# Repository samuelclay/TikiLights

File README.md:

# TikiLights
Hand-held tiki lights with color customization and a 3d printed Tiki mask

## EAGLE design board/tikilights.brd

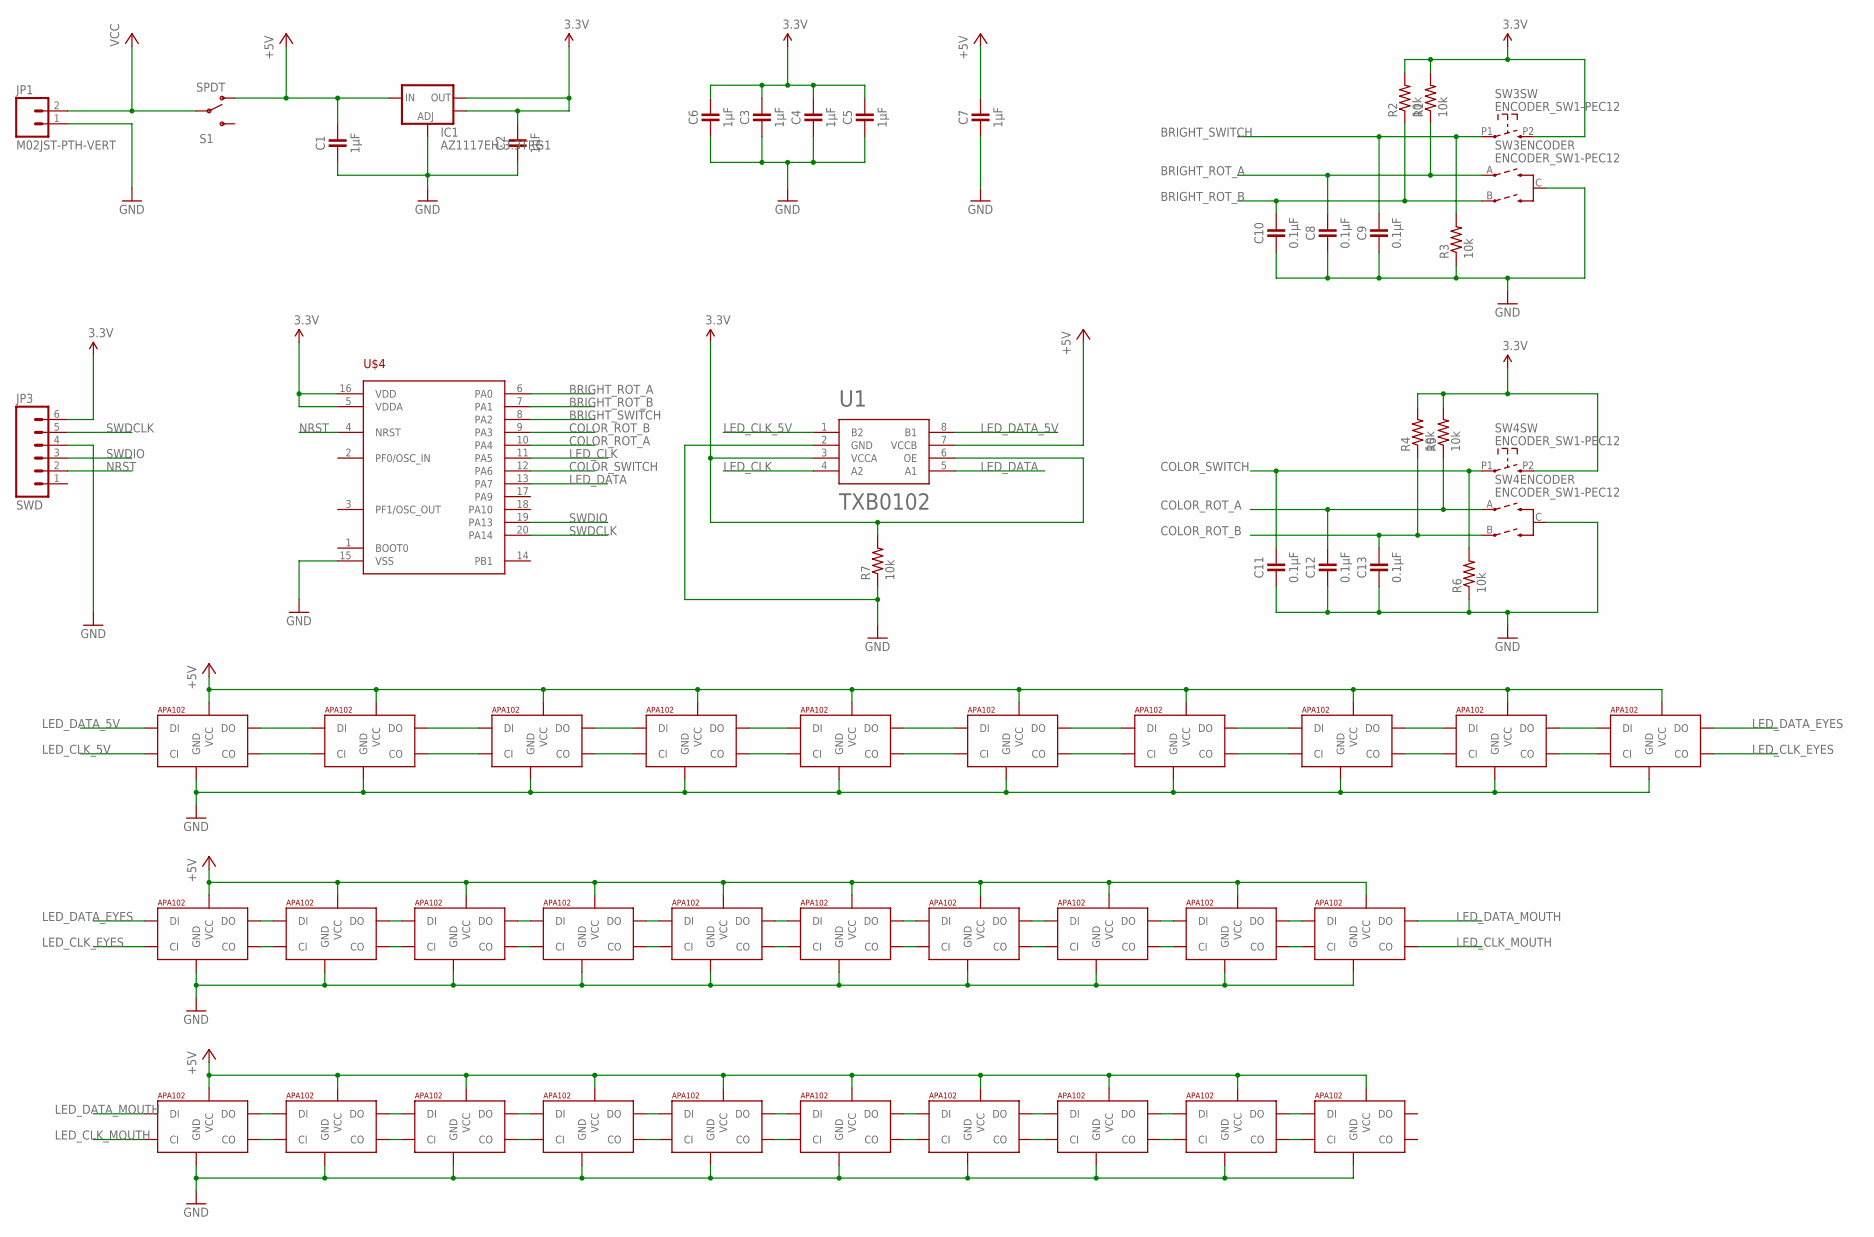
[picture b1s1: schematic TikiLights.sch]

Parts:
C1, C2, C3, C4, C5, C6, C7: 1µF; 0603_CAP
C8, C9, C10, C11, C12, C13: 0.1µF; 0603_CAP
IC1: AZ1117EH-3.3TRG1; SOT223
JP1: M02JST-PTH-VERT; JST-2-PTH-VERT
JP3: SWD; MOLEX-1X6
R1, R2, R3, R4, R5, R6, R7: 10k; 0603-RES
S1: SPDT; SWITCH-SPDT
SW3, SW4: ENCODER_SW1-PEC12; PEC12_INCREMENTAL_ENCODER
U1: TXB0102; SOP50P310X90-8N
U$1, U$2, U$3, U$5, U$6, U$27, U$28, U$29, U$30, U$31: APA1022020; APA102_2020
U$4: STM32F030F4; TSSOP20
U$7, U$8, U$9, U$10, U$11, U$12, U$13, U$14, U$15, U$16, U$17, U$18, U$19, U$20, U$21, U$22, U$23, U$24, U$25, U$26: APA1025050; APA102_5050

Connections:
3.3V: C2.1, C3.1, C4.1, C5.1, C6.1, IC1.2 (OUT), IC1.4 (OUT), JP3.6, R1.2, R2.2, R4.2, R5.2, R7.2, SW3.P2 (2), SW4.P2 (2), U1.3 (VCCA), U1.6 (OE), U$4.5 (VDDA), U$4.16 (VDD)
+5V: C1.1, C7.1, IC1.3 (IN), S1.1 (O), U1.7 (VCCB), U$1.V_CC (VCC), U$2.V_CC (VCC), U$3.V_CC (VCC), U$5.V_CC (VCC), U$6.V_CC (VCC), U$7.1 (VCC), U$8.1 (VCC), U$9.1 (VCC), U$10.1 (VCC), U$11.1 (VCC), U$12.1 (VCC), U$13.1 (VCC), U$14.1 (VCC), U$15.1 (VCC), U$16.1 (VCC), U$17.1 (VCC), U$18.1 (VCC), U$19.1 (VCC), U$20.1 (VCC), U$21.1 (VCC), U$22.1 (VCC), U$23.1 (VCC), U$24.1 (VCC), U$25.1 (VCC), U$26.1 (VCC), U$27.V_CC (VCC), U$28.V_CC (VCC), U$29.V_CC (VCC), U$30.V_CC (VCC), U$31.V_CC (VCC)
BRIGHT_ROT_A: C8.1, R1.1, SW3.A, U$4.6 (PA0)
BRIGHT_ROT_B: C10.1, R2.1, SW3.B, U$4.7 (PA1)
BRIGHT_SWITCH: C9.1, R3.2, SW3.P1 (1), U$4.8 (PA2)
COLOR_ROT_A: C12.1, R5.1, SW4.A, U$4.10 (PA4)
COLOR_ROT_B: C13.1, R4.1, SW4.B, U$4.9 (PA3)
COLOR_SWITCH: C11.1, R6.2, SW4.P1 (1), U$4.12 (PA6)
GND: C1.2, C2.2, C3.2, C4.2, C5.2, C6.2, C7.2, C8.2, C9.2, C10.2, C11.2, C12.2, C13.2, IC1.1 (ADJ), JP1.1, JP3.4, R3.1, R6.1, R7.1, SW3.C, SW4.C, U1.2 (GND), U$1.GND, U$2.GND, U$3.GND, U$4.15 (VSS), U$5.GND, U$6.GND, U$7.6 (GND), U$8.6 (GND), U$9.6 (GND), U$10.6 (GND), U$11.6 (GND), U$12.6 (GND), U$13.6 (GND), U$14.6 (GND), U$15.6 (GND), U$16.6 (GND), U$17.6 (GND), U$18.6 (GND), U$19.6 (GND), U$20.6 (GND), U$21.6 (GND), U$22.6 (GND), U$23.6 (GND), U$24.6 (GND), U$25.6 (GND), U$26.6 (GND), U$27.GND, U$28.GND, U$29.GND, U$30.GND, U$31.GND
LED_CLK: U1.4 (A2), U$4.11 (PA5)
LED_CLK_5V: U1.1 (B2), U$1.C_IN (CI)
LED_CLK_EYES: U$7.5 (CI), U$31.CL_OUT (CO)
LED_CLK_MOUTH: U$16.2 (CO), U$17.5 (CI)
LED_DATA: U1.5 (A1), U$4.13 (PA7)
LED_DATA_5V: U1.8 (B1), U$1.D_IN (DI)
LED_DATA_EYES: U$7.4 (DI), U$31.D_OUT (DO)
LED_DATA_MOUTH: U$16.3 (DO), U$17.4 (DI)
unnamed: U$1.D_OUT (DO), U$2.D_IN (DI)
unnamed: U$1.CL_OUT (CO), U$2.C_IN (CI)
unnamed: U$2.D_OUT (DO), U$3.D_IN (DI)
unnamed: U$2.CL_OUT (CO), U$3.C_IN (CI)
unnamed: U$3.D_OUT (DO), U$5.D_IN (DI)
unnamed: U$3.CL_OUT (CO), U$5.C_IN (CI)
unnamed: U$5.D_OUT (DO), U$6.D_IN (DI)
unnamed: U$5.CL_OUT (CO), U$6.C_IN (CI)
unnamed: U$6.D_OUT (DO), U$27.D_IN (DI)
unnamed: U$6.CL_OUT (CO), U$27.C_IN (CI)
unnamed: U$27.D_OUT (DO), U$28.D_IN (DI)
unnamed: U$27.CL_OUT (CO), U$28.C_IN (CI)
unnamed: U$28.D_OUT (DO), U$29.D_IN (DI)
unnamed: U$28.CL_OUT (CO), U$29.C_IN (CI)
unnamed: U$29.D_OUT (DO), U$30.D_IN (DI)
unnamed: U$29.CL_OUT (CO), U$30.C_IN (CI)
unnamed: U$30.D_OUT (DO), U$31.D_IN (DI)
unnamed: U$30.CL_OUT (CO), U$31.C_IN (CI)
unnamed: U$7.2 (CO), U$8.5 (CI)
unnamed: U$7.3 (DO), U$8.4 (DI)
unnamed: U$8.3 (DO), U$9.4 (DI)
unnamed: U$8.2 (CO), U$9.5 (CI)
unnamed: U$9.3 (DO), U$10.4 (DI)
unnamed: U$9.2 (CO), U$10.5 (CI)
unnamed: U$10.3 (DO), U$11.4 (DI)
unnamed: U$10.2 (CO), U$11.5 (CI)
unnamed: U$11.3 (DO), U$12.4 (DI)
unnamed: U$11.2 (CO), U$12.5 (CI)
unnamed: U$12.3 (DO), U$13.4 (DI)
unnamed: U$12.2 (CO), U$13.5 (CI)
unnamed: U$13.3 (DO), U$14.4 (DI)
unnamed: U$13.2 (CO), U$14.5 (CI)
unnamed: U$14.3 (DO), U$15.4 (DI)
unnamed: U$14.2 (CO), U$15.5 (CI)
unnamed: U$15.2 (CO), U$16.5 (CI)
unnamed: U$15.3 (DO), U$16.4 (DI)
unnamed: U$17.3 (DO), U$18.4 (DI)
unnamed: U$17.2 (CO), U$18.5 (CI)
unnamed: U$18.3 (DO), U$19.4 (DI)
unnamed: U$18.2 (CO), U$19.5 (CI)
unnamed: U$19.3 (DO), U$20.4 (DI)
unnamed: U$19.2 (CO), U$20.5 (CI)
unnamed: U$20.3 (DO), U$21.4 (DI)
unnamed: U$20.2 (CO), U$21.5 (CI)
unnamed: U$21.3 (DO), U$22.4 (DI)
unnamed: U$21.2 (CO), U$22.5 (CI)
unnamed: U$22.3 (DO), U$23.4 (DI)
unnamed: U$22.2 (CO), U$23.5 (CI)
unnamed: U$23.3 (DO), U$24.4 (DI)
unnamed: U$23.2 (CO), U$24.5 (CI)
unnamed: U$24.3 (DO), U$25.4 (DI)
unnamed: U$24.2 (CO), U$25.5 (CI)
unnamed: U$25.3 (DO), U$26.4 (DI)
unnamed: U$25.2 (CO), U$26.5 (CI)
NRST: JP3.2, U$4.4 (NRST)
SWDCLK: JP3.5, U$4.20 (PA14)
SWDIO: JP3.3, U$4.19 (PA13)
VCC: JP1.2, S1.2

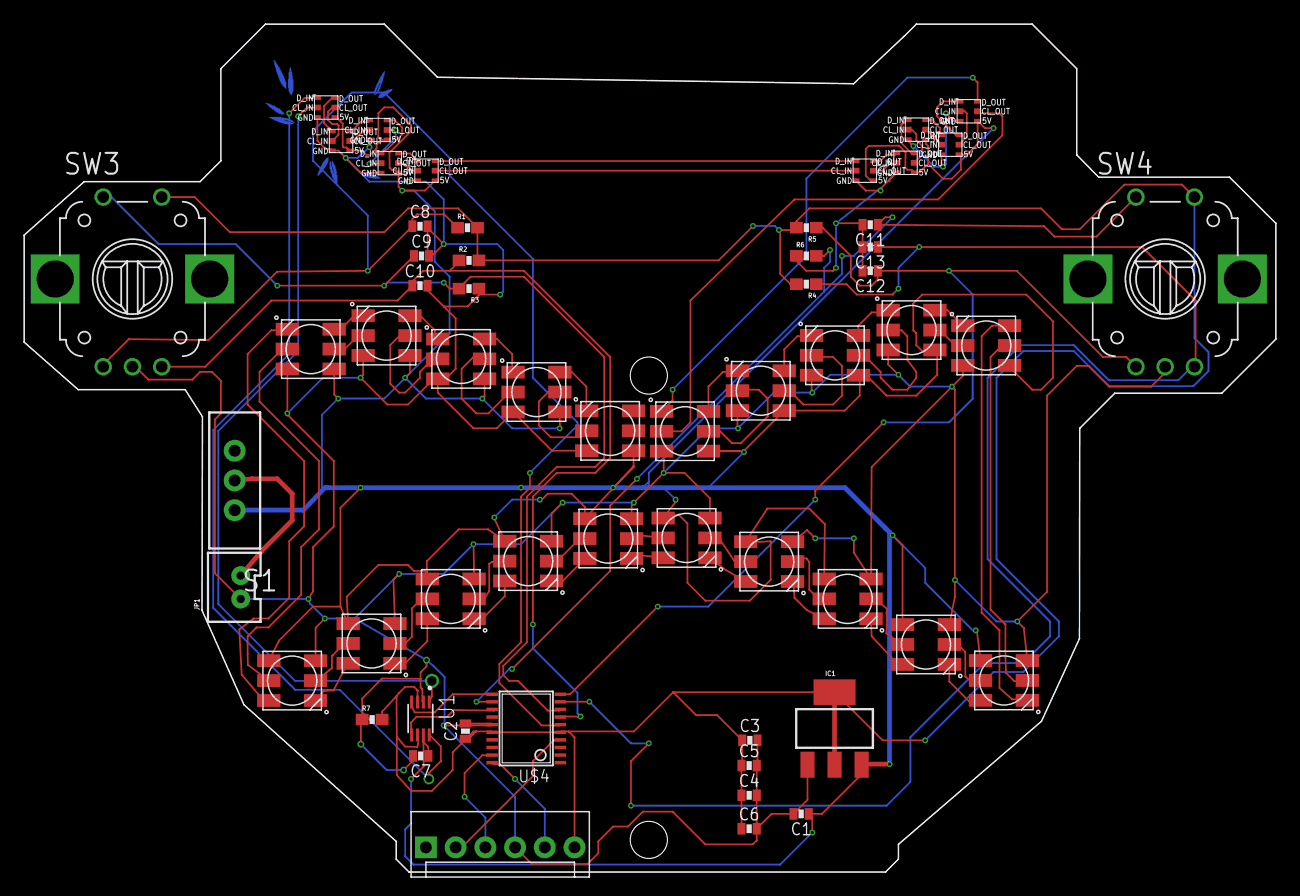
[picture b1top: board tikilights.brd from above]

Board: 2 copper layers, 107.0 x 72.5 mm, 60 parts (1 on the bottom side), 75 nets.

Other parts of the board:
U$32: KOALA
U$34: CAD-DRAWING

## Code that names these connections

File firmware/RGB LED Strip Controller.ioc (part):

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Mcu.Name=STM32F030F4Px
Mcu.Package=TSSOP20
Mcu.UserName=STM32F030F4Px
PA0.GPIOParameters=GPIO_Label,GPIO_ModeDefaultEXTI
PA0.GPIO_Label=ColorRotA
PA0.GPIO_ModeDefaultEXTI=GPIO_MODE_IT_RISING
PA0.Signal=GPXTI0
PA1.GPIOParameters=GPIO_Label
PA1.GPIO_Label=ColorRotB
PA1.Signal=GPIO_Input
PA13.Mode=Serial_Wire
PA13.Signal=SYS_SWDIO
PA14.Mode=Serial_Wire
PA14.Signal=SYS_SWCLK
PA2.GPIOParameters=GPIO_Label,GPIO_ModeDefaultEXTI
PA2.GPIO_Label=ColorButton
PA2.GPIO_ModeDefaultEXTI=GPIO_MODE_IT_RISING
PA2.Signal=GPXTI2
PA3.GPIOParameters=GPIO_Label
PA3.GPIO_Label=PwrRotB
PA3.Signal=GPIO_Input
PA4.GPIOParameters=GPIO_Label,GPIO_ModeDefaultEXTI
PA4.GPIO_Label=PwrRotA
PA4.GPIO_ModeDefaultEXTI=GPIO_MODE_IT_RISING
PA4.Signal=GPXTI4
PA5.Mode=Simplex_Bidirectional_Master
PA5.Signal=SPI1_SCK
PA6.GPIOParameters=GPIO_Label
PA6.GPIO_Label=PwrButton
PA6.Signal=GPXTI6
PA7.Mode=Simplex_Bidirectional_Master
PA7.Signal=SPI1_MOSI
PB1.GPIOParameters=GPIO_Label
PB1.GPIO_Label=Mode
PB1.Signal=GPIO_Input
RCC.SYSCLKFreq_VALUE=48000000
RCC.SYSCLKSource=RCC_SYSCLKSOURCE_PLLCLK
board=RGB LED Strip Controller

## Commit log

2018-02-26 Initial commit, stubbing in STM32F030 32-pin and 6-pin SWD Tag Connect programming header.
2018-03-16 Got the tiki mask outline in eagle. Still need to build the level shifter and then connect all the nets.
2018-03-16 Datasheets, eagle, and kicad. Nothing works yet.
2018-03-16 Deleting locks.
2018-03-17 Schematic is finished. Screw holes added. Need board layout and updated CAD model for dimensions.
2018-03-17 Updating board to fit resized mask. Battery pack now fits and everything is in place for routing. Mask still needs a hook, and board needs a message.
2018-03-17 Adjusting lights positioning.
2018-03-19 Submitting tikilights v1. Both board and cad. Hope I didn't forget anything!
2018-04-15 Revision 2. Fixing TXB0102 board. Widening encoder side drill holes.
2018-04-17 Adding demo app.
2018-05-01 Adding firmware and cleaning up unused board files.
2018-05-02 Custom printed ear control for rotary encoders.
2018-05-02 Updating Cube, adding random color button. Fixing SPI.
2018-05-03 Intensity button toggle between bright and dim.

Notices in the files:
parts and their libraries:
SparkFun-Aesthetics: Licensing: CC v3.0 Share-Alike You are welcome to use this library for commercial purposes.
